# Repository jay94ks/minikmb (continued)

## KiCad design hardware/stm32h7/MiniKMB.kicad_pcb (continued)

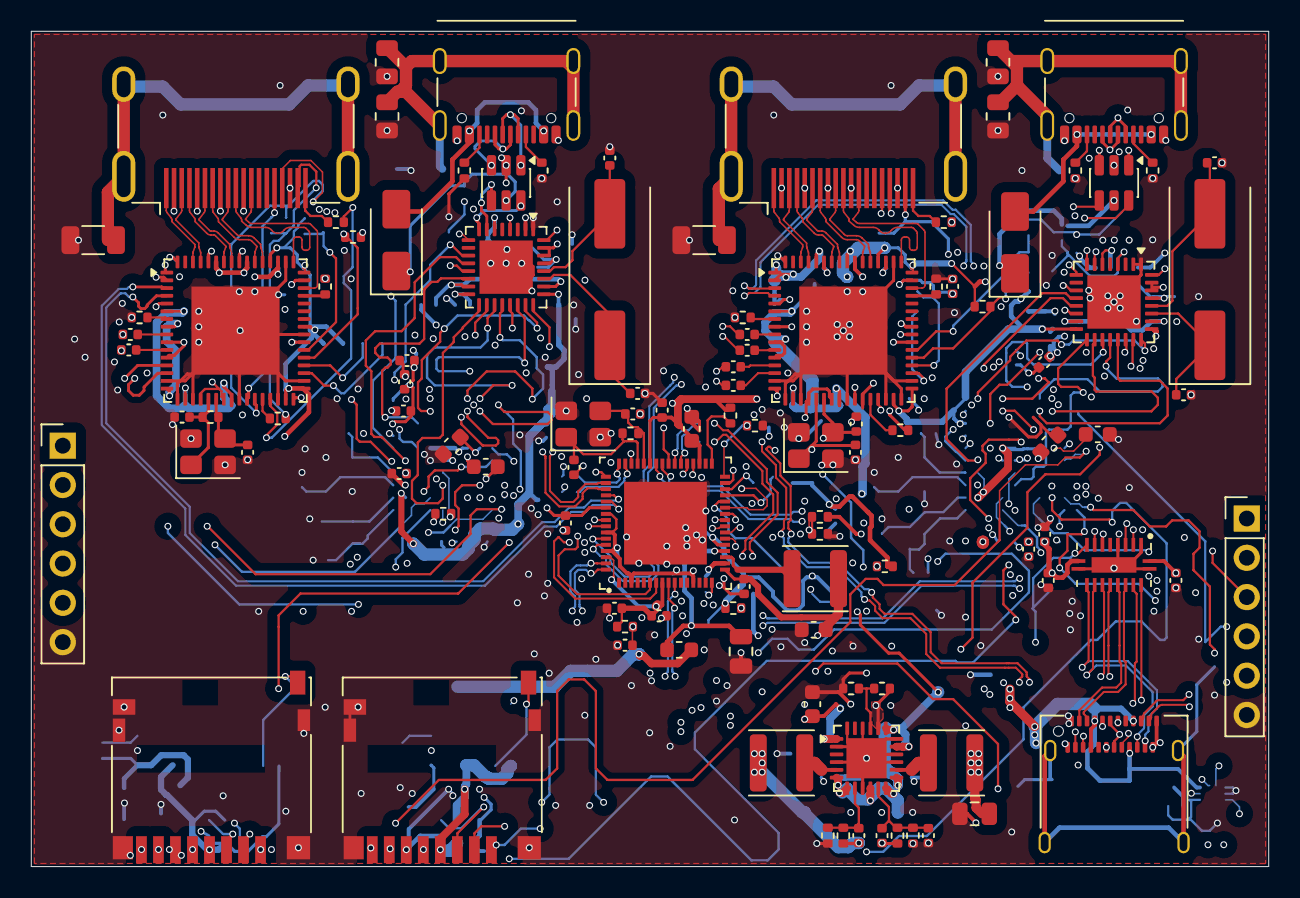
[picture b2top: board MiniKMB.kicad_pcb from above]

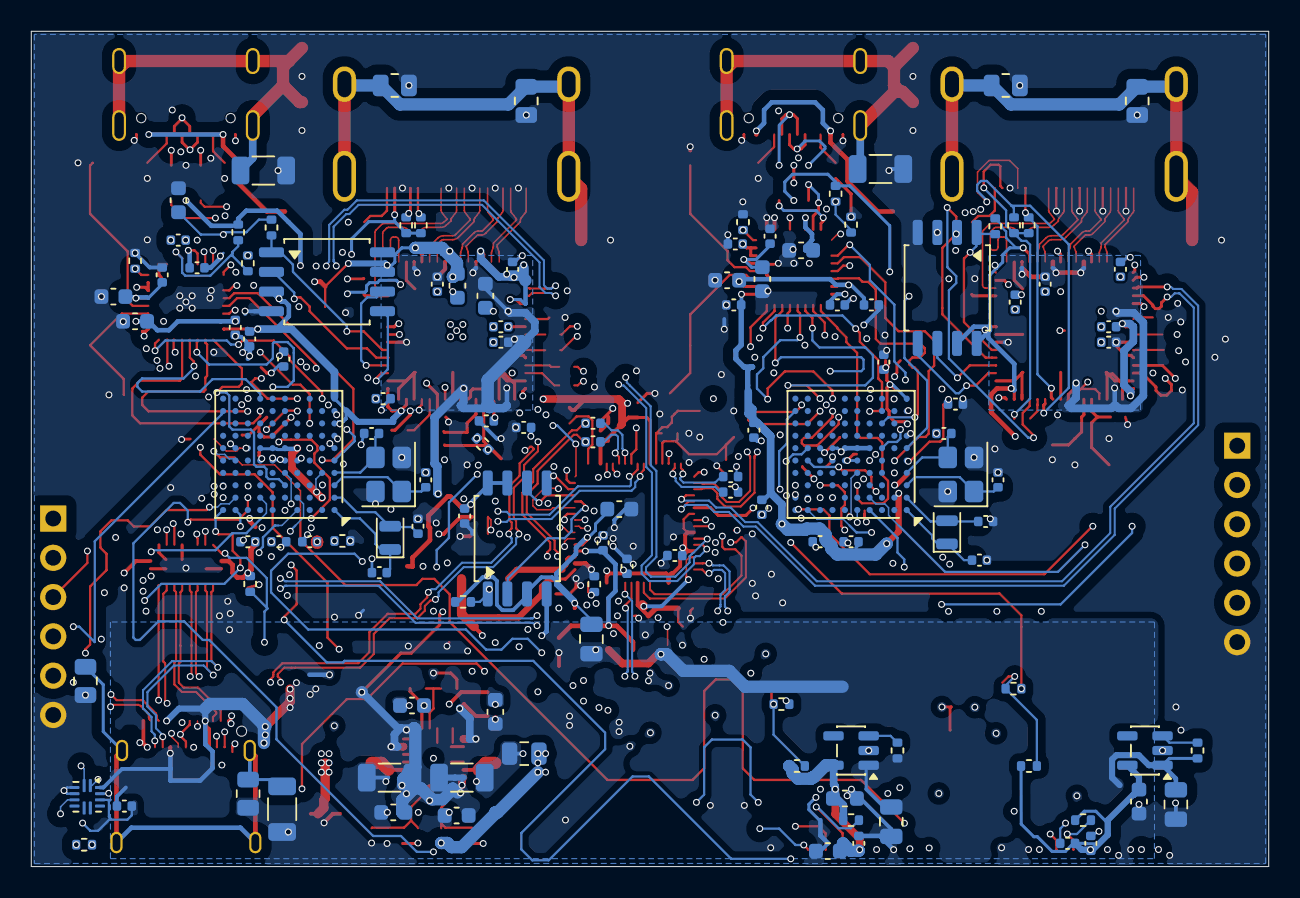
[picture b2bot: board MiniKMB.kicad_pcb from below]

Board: 6 copper layers, 80.0 x 54.0 mm, 230 parts (121 on the bottom side), 218 nets.

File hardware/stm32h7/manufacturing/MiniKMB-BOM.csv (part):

"Comment","Designator","Footprint","JLCPCB Part #"
"1nF/2kV 10%","C1","Capacitor_SMD:C_1206_3216Metric","C9196"
"1nF/2kV 10%","C2","Capacitor_SMD:C_1206_3216Metric","C9196"
"1nF/2kV 10%","C3","Capacitor_SMD:C_1206_3216Metric","C9196"
"1nF/2kV 10%","C4","Capacitor_SMD:C_1206_3216Metric","C9196"
"100nF 10%","C5","Capacitor_SMD:C_0402_1005Metric","C1525"
"10uF 20%","C6","Capacitor_SMD:C_0603_1608Metric","C96446"
"100nF 10%","C7","Capacitor_SMD:C_0402_1005Metric","C1525"
"10uF 20%","C8","Capacitor_SMD:C_0402_1005Metric","C3902158"
"22uF 20%","C9","Capacitor_SMD:C_0805_2012Metric","C45783"
"100nF 10%","C10","Capacitor_SMD:C_0402_1005Metric","C1525"
"100nF 10%","C11","Capacitor_SMD:C_0402_1005Metric","C1525"
"10uF 20%","C12","Capacitor_SMD:C_0603_1608Metric","C96446"
"100nF 10%","C13","Capacitor_SMD:C_0402_1005Metric","C1525"
"100nF 10%","C14","Capacitor_SMD:C_0402_1005Metric","C1525"
"30pF","C15","Capacitor_SMD:C_0402_1005Metric","C1570"
"30pF","C16","Capacitor_SMD:C_0402_1005Metric","C1570"
"30pF","C17","Capacitor_SMD:C_0402_1005Metric","C1570"
"30pF","C18","Capacitor_SMD:C_0402_1005Metric","C1570"
"22uF 20%","C19","Capacitor_SMD:C_0805_2012Metric","C45783"
"100nF 10%","C20","Capacitor_SMD:C_0402_1005Metric","C1525"
"10uF 20%","C21","Capacitor_SMD:C_0603_1608Metric","C96446"
"100nF 10%","C22","Capacitor_SMD:C_0402_1005Metric","C1525"
"100nF 10%","C23","Capacitor_SMD:C_0402_1005Metric","C1525"
"100nF 10%","C24","Capacitor_SMD:C_0402_1005Metric","C1525"
"100nF 10%","C25","Capacitor_SMD:C_0402_1005Metric","C1525"
"100nF 10%","C26","Capacitor_SMD:C_0402_1005Metric","C1525"
"100nF 10%","C27","Capacitor_SMD:C_0402_1005Metric","C1525"
"100nF 10%","C28","Capacitor_SMD:C_0402_1005Metric","C1525"
"100nF 10%","C29","Capacitor_SMD:C_0402_1005Metric","C1525"
"100nF 10%","C30","Capacitor_SMD:C_0402_1005Metric","C1525"
"100nF 10%","C31","Capacitor_SMD:C_0402_1005Metric","C1525"
"100nF 10%","C32","Capacitor_SMD:C_0402_1005Metric","C1525"
"18pF","C33","Capacitor_SMD:C_0402_1005Metric","C1549"
"18pF","C34","Capacitor_SMD:C_0402_1005Metric","C1549"
"18pF","C35","Capacitor_SMD:C_0402_1005Metric","C1549"
"18pF","C36","Capacitor_SMD:C_0402_1005Metric","C1549"
"10uF 20%","C37","Capacitor_SMD:C_0603_1608Metric","C96446"
"100nF 10%","C38","Capacitor_SMD:C_0402_1005Metric","C1525"
"10uF 20%","C39","Capacitor_SMD:C_0603_1608Metric","C96446"
"100nF 10%","C40","Capacitor_SMD:C_0402_1005Metric","C1525"
"100nF 10%","C41","Capacitor_SMD:C_0402_1005Metric","C1525"
"100nF 10%","C42","Capacitor_SMD:C_0402_1005Metric","C1525"
"100nF 10%","C43","Capacitor_SMD:C_0402_1005Metric","C1525"
"100nF 10%","C44","Capacitor_SMD:C_0402_1005Metric","C1525"
"100nF 10%","C45","Capacitor_SMD:C_0402_1005Metric","C1525"
"100nF 10%","C46","Capacitor_SMD:C_0402_1005Metric","C1525"
"4.7uF 10%","C47","Capacitor_SMD:C_0603_1608Metric","C69335"
"4.7uF 10%","C48","Capacitor_SMD:C_0603_1608Metric","C69335"
"4.7uF 10%","C49","Capacitor_SMD:C_0603_1608Metric","C69335"
"4.7uF 10%","C50","Capacitor_SMD:C_0603_1608Metric","C69335"
"100nF 10%","C51","Capacitor_SMD:C_0402_1005Metric","C1525"
"100nF 10%","C52","Capacitor_SMD:C_0402_1005Metric","C1525"
"100nF 10%","C53","Capacitor_SMD:C_0402_1005Metric","C1525"
"100nF 10%","C54","Capacitor_SMD:C_0402_1005Metric","C1525"
"18pF","C55","Capacitor_SMD:C_0402_1005Metric","C1549"
"18pF","C56","Capacitor_SMD:C_0402_1005Metric","C1549"
"2.2uF 10%","C57","Capacitor_SMD:C_0603_1608Metric","C100082"
"100nF 10%","C58","Capacitor_SMD:C_0402_1005Metric","C1525"
"100nF 10%","C59","Capacitor_SMD:C_0402_1005Metric","C1525"
"100nF 10%","C60","Capacitor_SMD:C_0402_1005Metric","C1525"
"2.2uF 10%","C61","Capacitor_SMD:C_0603_1608Metric","C100082"
"100nF 10%","C62","Capacitor_SMD:C_0402_1005Metric","C1525"
"100nF 10%","C63","Capacitor_SMD:C_0402_1005Metric","C1525"
"100nF 10%","C64","Capacitor_SMD:C_0402_1005Metric","C1525"
"100nF 10%","C65","Capacitor_SMD:C_0402_1005Metric","C1525"
"100nF 10%","C66","Capacitor_SMD:C_0402_1005Metric","C1525"
"10pF","C67","Capacitor_SMD:C_0402_1005Metric","C1545"
"10uF 20%","C68","Capacitor_SMD:C_0603_1608Metric","C96446"
"10uF 20%","C69","Capacitor_SMD:C_0603_1608Metric","C96446"
"100nF 10%","C70","Capacitor_SMD:C_0402_1005Metric","C1525"
"10uF 20%","C71","Capacitor_SMD:C_0603_1608Metric","C96446"
"100nF 10%","C72","Capacitor_SMD:C_0402_1005Metric","C1525"
"100nF 10%","C73","Capacitor_SMD:C_0402_1005Metric","C1525"
"100nF 10%","C74","Capacitor_SMD:C_0402_1005Metric","C1525"
"100nF 10%","C75","Capacitor_SMD:C_0402_1005Metric","C1525"
"100nF 10%","C76","Capacitor_SMD:C_0402_1005Metric","C1525"
"10pF","C77","Capacitor_SMD:C_0402_1005Metric","C1545"
"100nF 10%","C78","Capacitor_SMD:C_0402_1005Metric","C1525"
"10uF 10%","C79","Capacitor_SMD:C_0805_2012Metric","C2932476"
"100nF 10%","C80","Capacitor_SMD:C_0402_1005Metric","C1525"
"18pF","C81","Capacitor_SMD:C_0402_1005Metric","C1549"
"18pF","C82","Capacitor_SMD:C_0402_1005Metric","C1549"
"10uF 10%","C83","Capacitor_SMD:C_0805_2012Metric","C2932476"
"100nF 10%","C84","Capacitor_SMD:C_0402_1005Metric","C1525"
"100nF 10%","C85","Capacitor_SMD:C_0402_1005Metric","C1525"
"18pF","C86","Capacitor_SMD:C_0402_1005Metric","C1549"
"100nF 10%","C87","Capacitor_SMD:C_0402_1005Metric","C1525"
"18pF","C88","Capacitor_SMD:C_0402_1005Metric","C1549"
"2.2uF 10%","C89","Capacitor_SMD:C_0603_1608Metric","C100082"
"100nF 10%","C90","Capacitor_SMD:C_0402_1005Metric","C1525"
"100nF 10%","C91","Capacitor_SMD:C_0402_1005Metric","C1525"
"100nF 10%","C92","Capacitor_SMD:C_0402_1005Metric","C1525"
"2.2uF 10%","C93","Capacitor_SMD:C_0603_1608Metric","C100082"
"100nF 10%","C94","Capacitor_SMD:C_0402_1005Metric","C1525"
"100nF 10%","C95","Capacitor_SMD:C_0402_1005Metric","C1525"
"22uF 10%","C96","Capacitor_SMD:C_1206_3216Metric","C12891"
"22uF 10%","C97","Capacitor_SMD:C_1206_3216Metric","C12891"
"4.7uF 10%","C98","Capacitor_SMD:C_0603_1608Metric","C69335"
"4.7uF 10%","C99","Capacitor_SMD:C_0603_1608Metric","C69335"
"100nF 10%","C100","Capacitor_SMD:C_0402_1005Metric","C1525"
"100nF 10%","C101","Capacitor_SMD:C_0402_1005Metric","C1525"
"100nF 10%","C102","Capacitor_SMD:C_0402_1005Metric","C1525"
"10uF 20%","C103","Capacitor_SMD:C_0603_1608Metric","C96446"
"4.7uF 10%","C104","Capacitor_SMD:C_0603_1608Metric","C69335"
"10pF","C105","Capacitor_SMD:C_0402_1005Metric","C1545"
"15pF 5%","C106","Capacitor_SMD:C_0402_1005Metric","C1548"
"10pF","C107","Capacitor_SMD:C_0402_1005Metric","C1545"
"68pF 5%","C108","Capacitor_SMD:C_0402_1005Metric","C76977"
"330pF 5%","C109","Capacitor_SMD:C_0402_1005Metric","C76965"
"22uF 20%","C110","Capacitor_SMD:C_0805_2012Metric","C602037"
"10uF 20%","C111","Capacitor_SMD:C_0603_1608Metric","C96446"
"10uF 20%","C112","Capacitor_SMD:C_0603_1608Metric","C96446"
"100nF 10%","C113","Capacitor_SMD:C_0402_1005Metric","C1525"
"100nF 10%","C114","Capacitor_SMD:C_0402_1005Metric","C1525"
"10uF 20%","C115","Capacitor_SMD:C_0402_1005Metric","C3902158"
"22uF 20%","C116","Capacitor_SMD:C_0805_2012Metric","C602037"
"100nF 10%","C117","Capacitor_SMD:C_0402_1005Metric","C1525"
"100nF 10%","C118","Capacitor_SMD:C_0402_1005Metric","C1525"
"100nF 10%","C119","Capacitor_SMD:C_0402_1005Metric","C1525"
"10uF 20%","C120","Capacitor_SMD:C_0603_1608Metric","C96446"
"100nF 10%","C121","Capacitor_SMD:C_0402_1005Metric","C1525"
"100nF 10%","C122","Capacitor_SMD:C_0402_1005Metric","C1525"
"1nF/2kV 10%","C123","Capacitor_SMD:C_1206_3216Metric","C9196"
"SS34","D1","Diode_SMD:D_SMA","C8678"
"SS34","D2","Diode_SMD:D_SMA","C8678"
"USB_C_Receptacle_USB2.0_16P","J3","Connector_USB:USB_C_Receptacle_Palconn_UTC16-G","C165948"
"USB_C_Receptacle_USB2.0_16P","J4","Connector_USB:USB_C_Receptacle_Palconn_UTC16-G","C165948"
"SWD","J5","Connector_PinHeader_2.54mm:PinHeader_1x06_P2.54mm_Vertical","C492405"
"SWD","J6","Connector_PinHeader_2.54mm:PinHeader_1x06_P2.54mm_Vertical","C492405"
"DM3D-SF","J7","Connector_Card:microSD_HC_Hirose_DM3D-SF","C719027"
"DM3D-SF","J8","Connector_Card:microSD_HC_Hirose_DM3D-SF","C719027"
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
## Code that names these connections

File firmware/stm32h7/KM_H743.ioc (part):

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Mcu.Name=STM32H743V(G-I)Hx
Mcu.Package=TFBGA100
Mcu.UserName=STM32H743VIHx
PA11.Mode=Device_Only
PA11.Signal=USB_OTG_FS_DM
PA12.Mode=Device_Only
PA12.Signal=USB_OTG_FS_DP
PA13\ (JTMS/SWDIO).Mode=Serial_Wire
PA13\ (JTMS/SWDIO).Signal=DEBUG_JTMS-SWDIO
PA14\ (JTCK/SWCLK).Mode=Serial_Wire
PA14\ (JTCK/SWCLK).Signal=DEBUG_JTCK-SWCLK
PA3.Mode=Device_HS
PA3.Signal=USB_OTG_HS_ULPI_D0
PA5.Mode=Device_HS
PA5.Signal=USB_OTG_HS_ULPI_CK
PB0.Mode=Device_HS
PB0.Signal=USB_OTG_HS_ULPI_D1
PB1.Mode=Device_HS
PB1.Signal=USB_OTG_HS_ULPI_D2
PB10.Mode=Device_HS
PB10.Signal=USB_OTG_HS_ULPI_D3
PB11.Mode=Device_HS
PB11.Signal=USB_OTG_HS_ULPI_D4
PB12.Mode=Device_HS
PB12.Signal=USB_OTG_HS_ULPI_D5
PB13.Mode=Device_HS
PB13.Signal=USB_OTG_HS_ULPI_D6
PB5.Mode=Device_HS
PB5.Signal=USB_OTG_HS_ULPI_D7
PB7.GPIOParameters=GPIO_Label
PB7.GPIO_Label=USB_ULPI_RST
PB7.Signal=GPIO_Output
PB8.Mode=Asynchronous
PB8.Signal=UART4_RX
PB9.Mode=Asynchronous
PB9.Signal=UART4_TX
PC0.Mode=Device_HS
PC0.Signal=USB_OTG_HS_ULPI_STP
PC10.Mode=SD_4_bits_Wide_bus
PC10.Signal=SDMMC1_D2
PC11.Mode=SD_4_bits_Wide_bus
PC11.Signal=SDMMC1_D3
PC12.Mode=SD_4_bits_Wide_bus
PC12.Signal=SDMMC1_CK
PC14-OSC32_IN\ (OSC32_IN).GPIOParameters=PinAttribute
PC14-OSC32_IN\ (OSC32_IN).Mode=LSE-External-Oscillator
PC14-OSC32_IN\ (OSC32_IN).PinAttribute=Free
PC14-OSC32_IN\ (OSC32_IN).Signal=RCC_OSC32_IN
PC15-OSC32_OUT\ (OSC32_OUT).Mode=LSE-External-Oscillator
PC15-OSC32_OUT\ (OSC32_OUT).Signal=RCC_OSC32_OUT
PC2_C.Mode=Device_HS
PC2_C.Signal=USB_OTG_HS_ULPI_DIR
PC3_C.Mode=Device_HS
PC3_C.Signal=USB_OTG_HS_ULPI_NXT
PC8.Mode=SD_4_bits_Wide_bus
PC8.Signal=SDMMC1_D0
PC9.Mode=SD_4_bits_Wide_bus
PC9.Signal=SDMMC1_D1
PD13.GPIOParameters=GPIO_Label
PD13.GPIO_Label=SDMMC1_DET
PD13.Signal=GPIO_Input
PD2.Mode=SD_4_bits_Wide_bus
PD2.Signal=SDMMC1_CMD
PH0-OSC_IN\ (PH0).Mode=HSE-External-Oscillator
PH0-OSC_IN\ (PH0).Signal=RCC_OSC_IN
PH1-OSC_OUT\ (PH1).Mode=HSE-External-Oscillator
PH1-OSC_OUT\ (PH1).Signal=RCC_OSC_OUT
RCC.HSE_VALUE=25000000
RCC.SYSCLKFreq_VALUE=480000000
RCC.SYSCLKSource=RCC_SYSCLKSOURCE_PLLCLK
board=custom
